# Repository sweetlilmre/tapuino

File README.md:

# Tapuino

This project is now in maintanence mode and has been superseeded by the [Tapuino Next](https://github.com/sweetlilmre/TapuinoNext)

However amazing people keep building this version and adding value (see the [3D printable enclosure below](#3d-printable-enclosure))

Limited support can be found in the following Amibay forum [Amibay](https://www.amibay.com/threads/tapuino-the-20-c64-tape-emulator.64874)

## The $20 C64 Tape Emulator

Details can be found on my blog: http://www.sweetlilmre.com

The FAQ and other docs can be found on the wiki: https://github.com/sweetlilmre/tapuino/wiki

A really nice board design can be found here: https://github.com/arananet/tapuinomini1.03

And a write up here: http://arananet-net.kinja.com/tapuino-1-03-mejorando-el-tapuino-mini-1788202676

These schematics are also provided in the "layout" folder as a convenience. 

Portions of this code are copyright by their respective owners:

 * PetitFatfs: Chan: http://elm-chan.org/fsw/ff/00index_p.html
 * I2C code: Peter Fleury <pfleury@gmx.ch>  http://jump.to/fleury
 * LCD code: conversion of the Arduino code apparently by DFRobot? (converted to C by me)

## 3D printable enclosure
by @fabriziofiorucci

A [3D printable enclosure](CAD) designed with Fusion 360 is available for download as .stl files

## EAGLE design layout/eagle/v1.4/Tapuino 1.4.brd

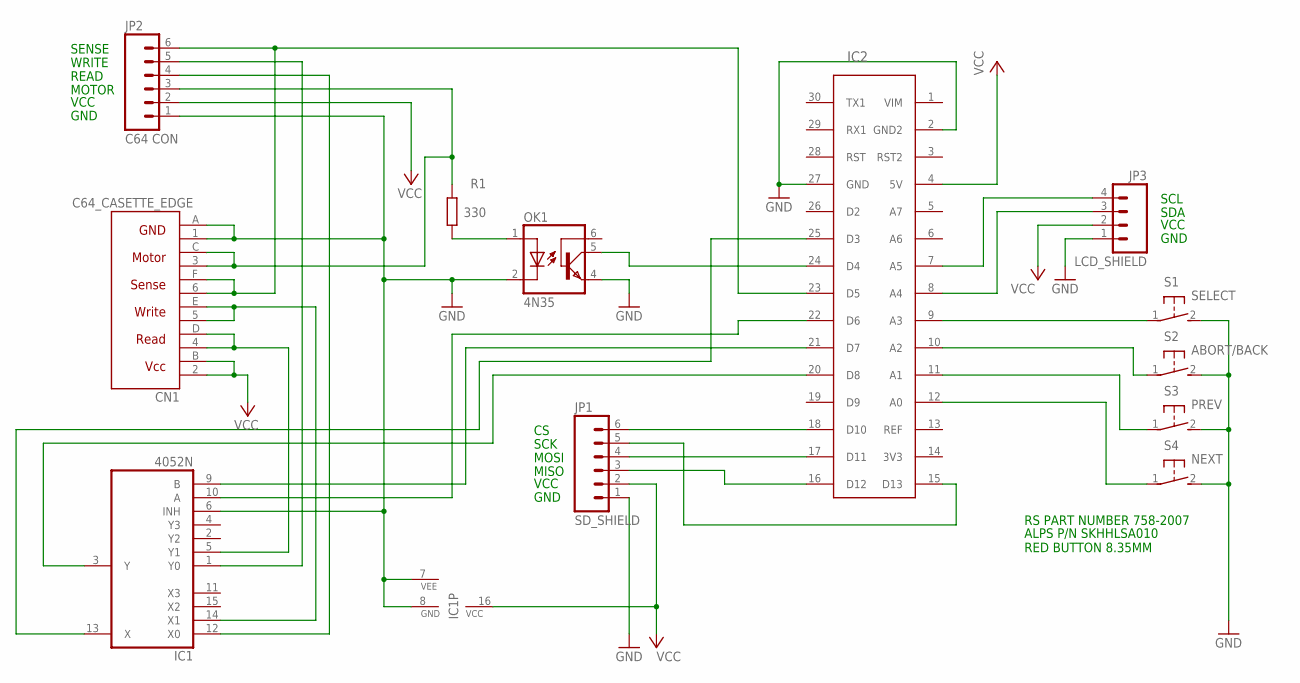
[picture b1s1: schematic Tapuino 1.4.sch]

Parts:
CN1: C64_CASETTE_EDGE; C64_CASSETTE
IC1: 4052N; DIL16
IC2: ARDUINO_NANO_V3; NANO_V3
JP1: SD_SHIELD; 1X06_LOCK_LONGPADS
JP2: C64 CON; 1X06_LOCK_LONGPADS
JP3: LCD_SHIELD; 1X04_LOCK_LONGPADS
OK1: 4N35; DIL06
R1: 330; 0207/10
S1: SELECT; B3F-31XX
S2: ABORT/BACK; B3F-31XX
S3: PREV; B3F-31XX
S4: NEXT; B3F-31XX

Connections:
GND: CN1.1 (GND1), CN1.A (GND2), IC1.6 (INH), IC1.7 (VEE), IC1.8 (GND), IC2.2 (GND2), IC2.27 (GND), JP1.1, JP2.1, JP3.1, OK1.2 (C), OK1.4 (EMI), S1.2 (S), S2.2 (S), S3.2 (S), S4.2 (S)
unnamed: IC2.16 (D12), JP1.3
unnamed: IC2.18 (D10), JP1.6
unnamed: IC2.15 (D13), JP1.5
unnamed: IC2.17 (D11), JP1.4
unnamed: IC2.7 (A5), JP3.4
unnamed: IC2.8 (A4), JP3.3
unnamed: IC2.9 (A3), S1.1
unnamed: OK1.1 (A), R1.1
unnamed: IC2.12 (A0), S4.1
unnamed: IC2.24 (D4), OK1.5 (COL)
unnamed: IC2.11 (A1), S3.1
unnamed: IC1.1 (Y0), JP2.5
unnamed: CN1.3 (MOTOR1), CN1.C (MOTOR2), JP2.3, R1.2
unnamed: IC1.3 (Y), IC2.20 (D8)
unnamed: IC1.12 (X0), JP2.4
unnamed: CN1.6 (SENSE1), CN1.F (SENSE2), IC2.23 (D5), JP2.6
unnamed: IC1.13 (X), IC2.25 (D3)
unnamed: CN1.4 (READ1), CN1.D (READ2), IC1.5 (Y1)
unnamed: IC1.9 (B), IC2.21 (D7)
unnamed: CN1.5 (WRITE1), CN1.E (WRITE2), IC1.14 (X1)
unnamed: IC1.10 (A), IC2.22 (D6)
unnamed: IC2.10 (A2), S2.1
VCC: CN1.2 (VCC1), CN1.B (VCC2), IC1.16 (VCC), IC2.4 (5V), JP1.2, JP2.2, JP3.2

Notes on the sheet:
SCK
MOSI
MISO
VCC
GND
SCL
SDA
SENSE
WRITE
READ
MOTOR
RS PART NUMBER 758-2007
ALPS P/N SKHHLSA010 RED BUTTON 8.35MM

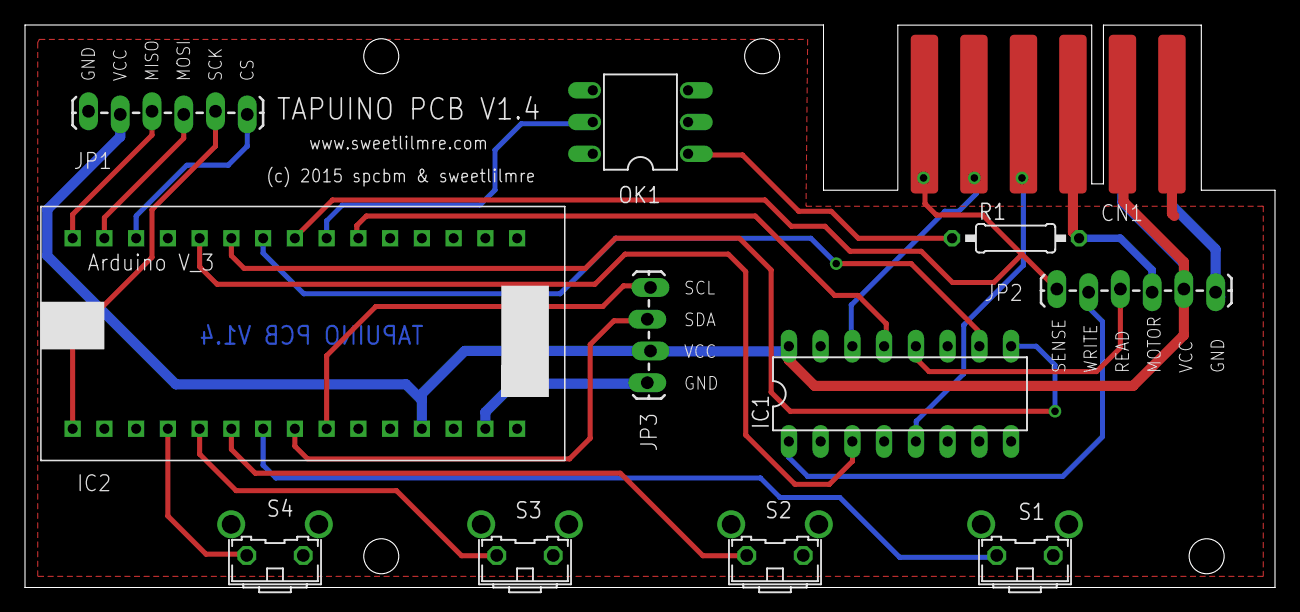
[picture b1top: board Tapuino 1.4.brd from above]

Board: 2 copper layers, 100.0 x 45.0 mm, 12 parts (0 on the bottom side), 24 nets.

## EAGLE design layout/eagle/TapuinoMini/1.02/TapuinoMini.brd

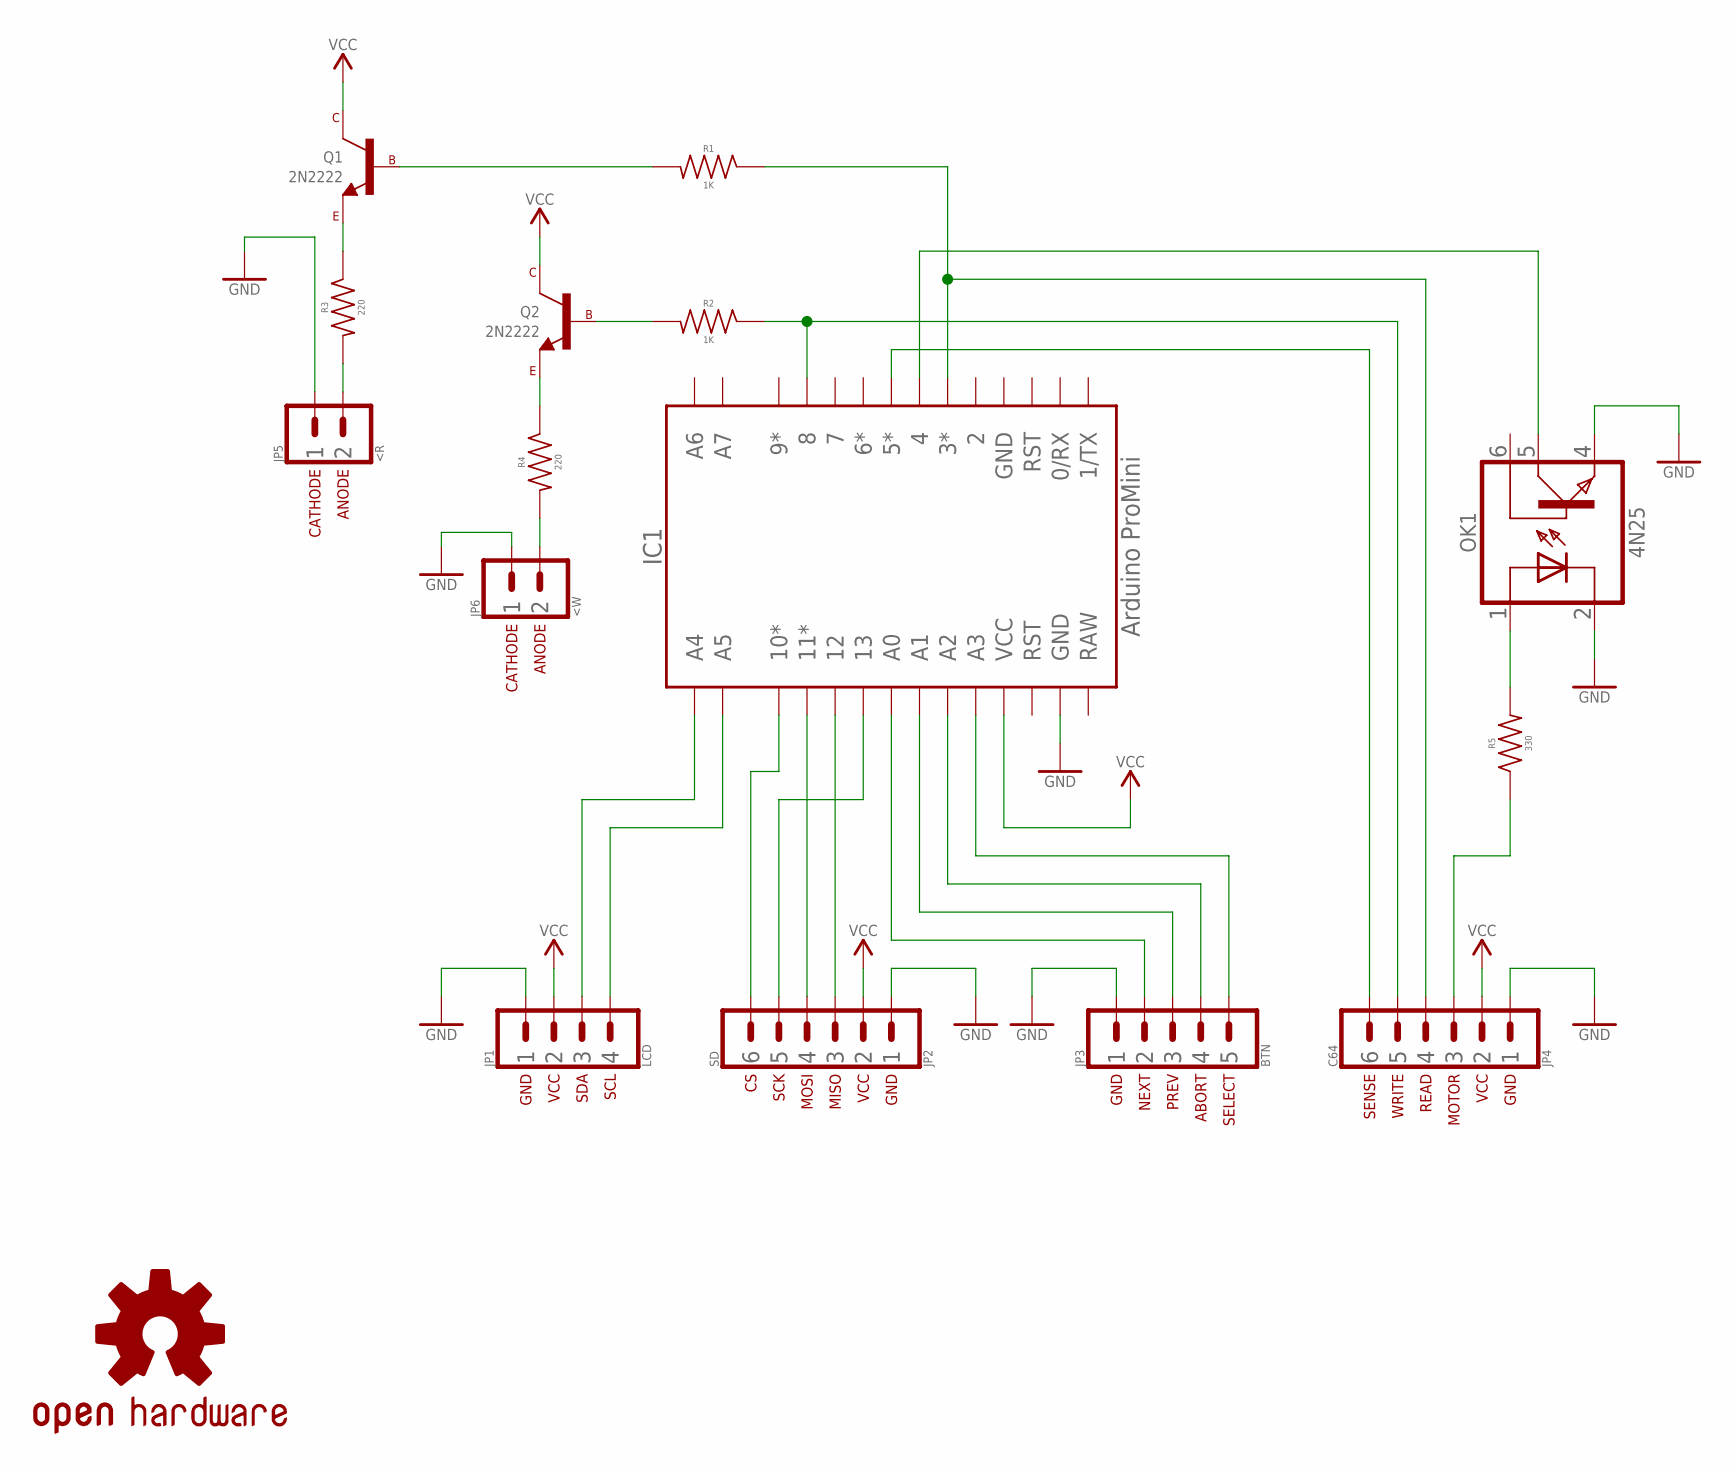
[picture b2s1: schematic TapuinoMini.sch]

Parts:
IC1: Arduino ProMini; PROMINI_A
JP1: LCD; 1X04_SQR
JP2: SD; 1X06_SQR
JP3: BTN; 1X05_SQR
JP4: C64; 1X06_SQR
JP5: <R; 1X02_SQR
JP6: <W; 1X02_SQR
LOGO1: OSHW-LOGOL; OSHW-LOGO-L
OK1: 4N25; DIP06
Q1, Q2: 2N2222; TO-92
R1, R2: 1K; RESISTOR_PTH_0.3
R3, R4: 220; RESISTOR_PTH_0.3
R5: 330; RESISTOR_PTH_0.3

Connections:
ABORT: IC1.A2, JP3.4
CS: IC1.10*, JP2.6
GND: IC1.GND@1 (GND), JP1.1, JP2.1, JP3.1, JP4.1, JP5.1, JP6.1, OK1.2 (CATHODE), OK1.4 (EMITTER)
MISO: IC1.12, JP2.3
MOSI: IC1.11*, JP2.4
MOTOR1: JP4.3, R5.1
MOTOR2: OK1.1 (ANODE), R5.2
MOTOR3: IC1.4, OK1.5 (COLLECTOR)
NEXT: IC1.A0, JP3.2
PREV: IC1.A1, JP3.3
READ1: IC1.3*, JP4.4, R1.1
READ2: Q1.2 (BASE), R1.2
READ3: Q1.1 (EMITTER), R3.1
READ4: JP5.2, R3.2
SCK: IC1.13, JP2.5
SCL: IC1.A5, JP1.4
SDA: IC1.A4, JP1.3
SELECT: IC1.A3, JP3.5
SENSE: IC1.5*, JP4.6
VCC: IC1.VCC, JP1.2, JP2.2, JP4.2, Q1.3 (COLLECTOR), Q2.3 (COLLECTOR)
WRITE1: IC1.8, JP4.5, R2.1
WRITE2: Q2.2 (BASE), R2.2
WRITE3: Q2.1 (EMITTER), R4.1
WRITE4: JP6.2, R4.2

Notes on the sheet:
GND
VCC
SDA
SCL
SCK
MISO
MOSI
NEXT
PREV
ABORT
SELECT
MOTOR
READ
WRITE
SENSE
CATHODE
ANODE

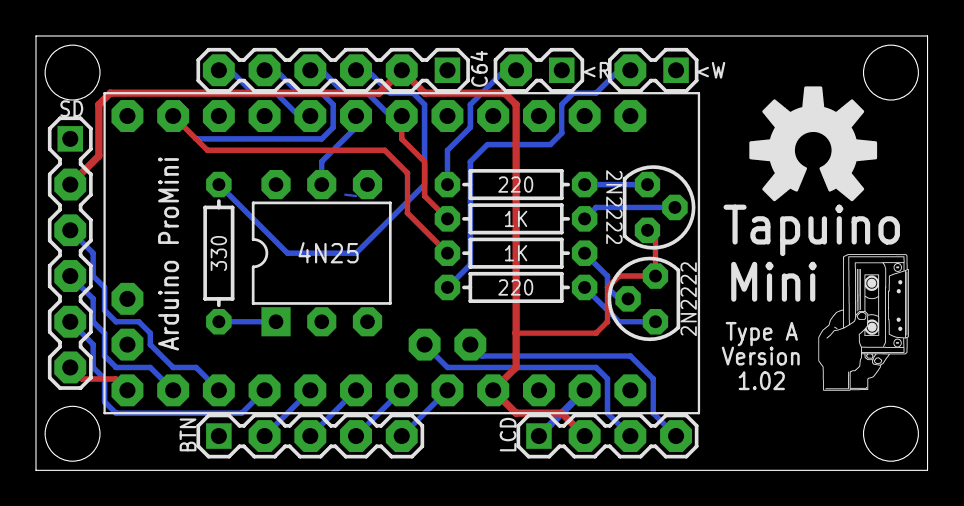
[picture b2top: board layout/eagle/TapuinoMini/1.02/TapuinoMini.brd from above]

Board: 2 copper layers, 49.5 x 24.1 mm, 16 parts (0 on the bottom side), 24 nets.

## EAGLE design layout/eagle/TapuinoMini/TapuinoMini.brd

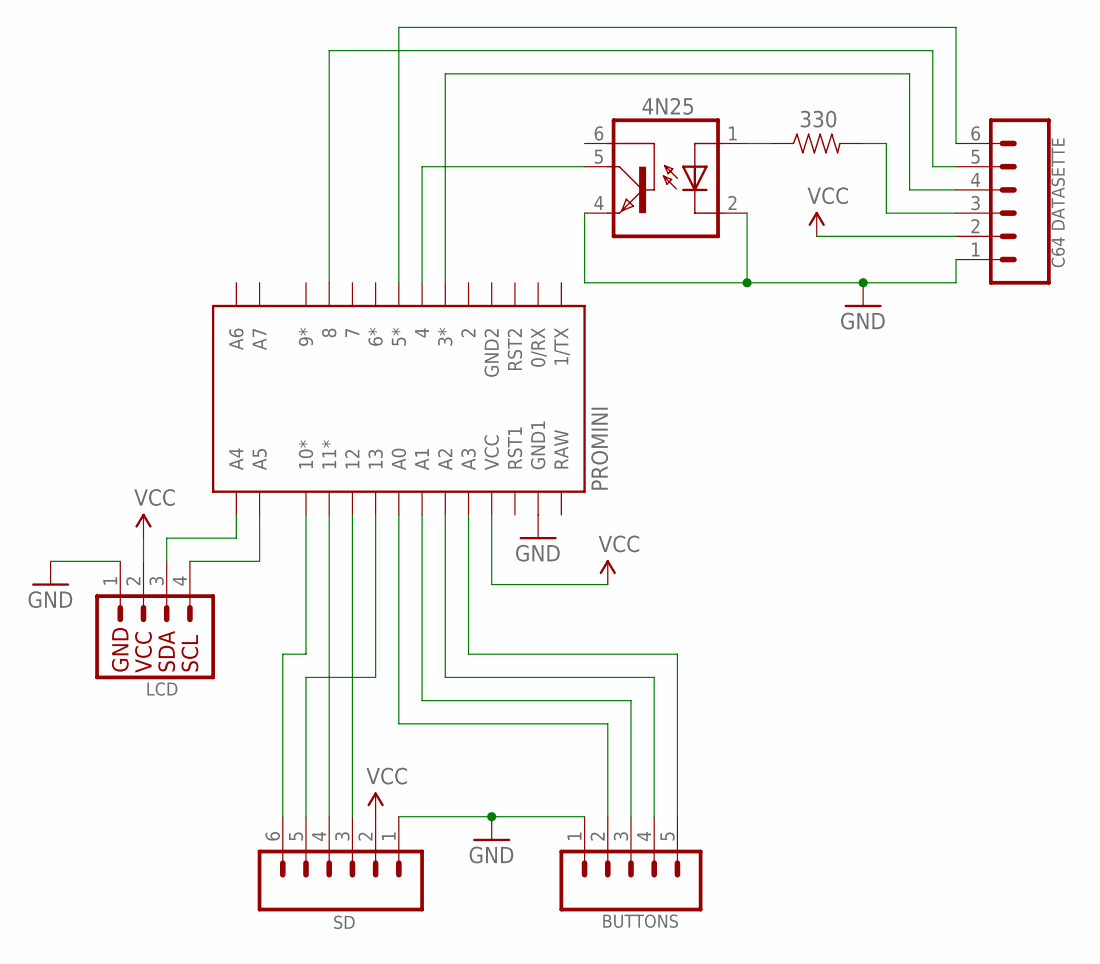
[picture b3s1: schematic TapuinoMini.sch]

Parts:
JP1: C64 DATASETTE; 1X06
JP2: SD; 1X06
JP3: BUTTONS; 1X05
JP4: LCD; 1X04
OK1: 4N25; DIL06
PROMINI: PROMINI_A
R1: 330; AXIAL-0.3

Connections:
GND: JP1.1, JP2.1, JP3.1, JP4.1, OK1.2 (C), OK1.4 (EMI), PROMINI.GND1
unnamed: JP3.5, PROMINI.A3
unnamed: JP3.4, PROMINI.A2
unnamed: JP3.3, PROMINI.A1
unnamed: JP3.2, PROMINI.A0
unnamed: JP2.3, PROMINI.12
unnamed: JP2.4, PROMINI.11*
unnamed: JP2.6, PROMINI.10*
unnamed: JP2.5, PROMINI.13
unnamed: JP4.4, PROMINI.A5
unnamed: JP4.3, PROMINI.A4
unnamed: JP1.3, R1.P$2 (2)
unnamed: OK1.1 (A), R1.P$1 (1)
unnamed: JP1.4, PROMINI.3*
unnamed: OK1.5 (COL), PROMINI.4
unnamed: JP1.5, PROMINI.8
unnamed: JP1.6, PROMINI.5*
VCC: JP1.2, JP2.2, JP4.2, PROMINI.VCC

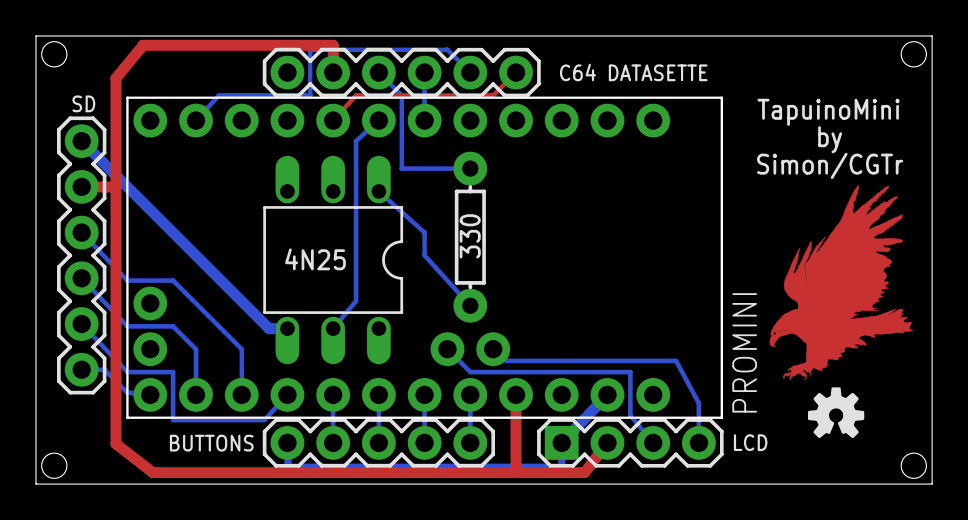
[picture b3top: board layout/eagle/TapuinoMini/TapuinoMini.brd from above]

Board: 2 copper layers, 49.8 x 24.9 mm, 9 parts (0 on the bottom side), 18 nets.

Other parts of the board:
U$2: EAGLE-TOP-8MM
U$3: OSHW-LOGO-S

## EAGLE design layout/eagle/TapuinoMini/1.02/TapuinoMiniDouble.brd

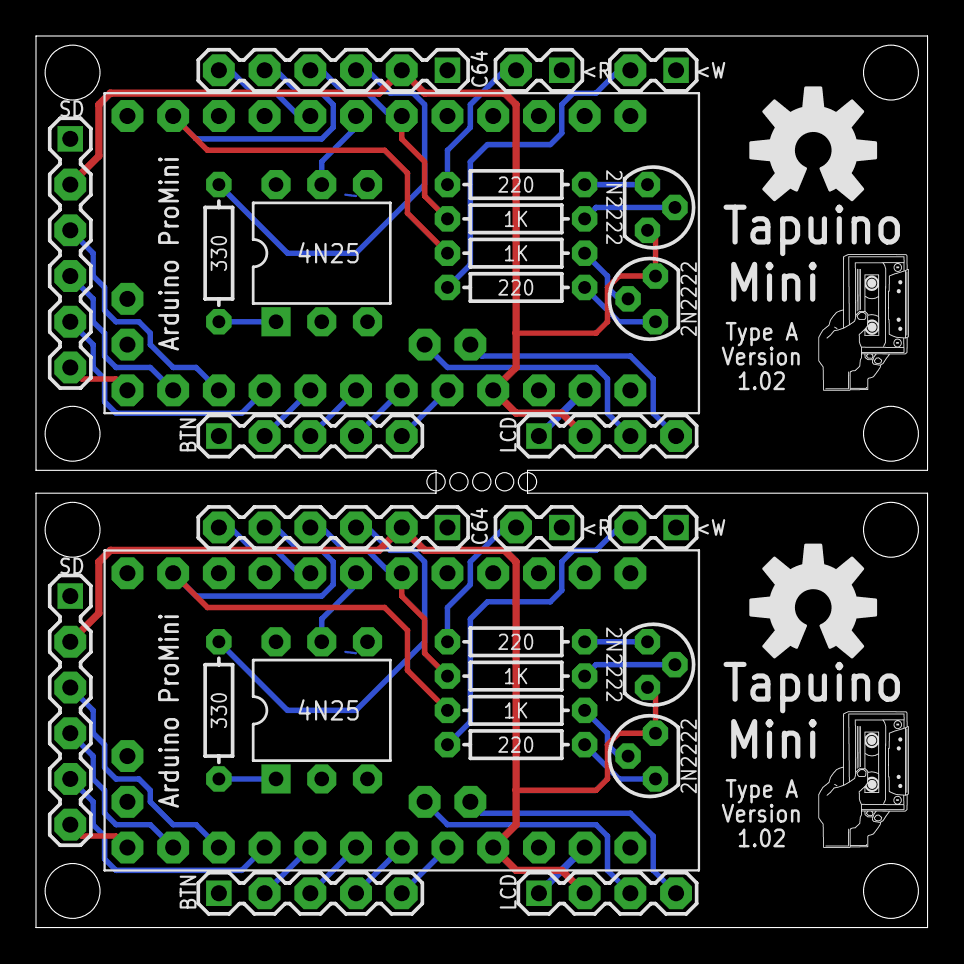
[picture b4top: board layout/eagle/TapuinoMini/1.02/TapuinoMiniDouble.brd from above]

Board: 2 copper layers, 49.5 x 49.5 mm, 32 parts (0 on the bottom side), 48 nets.

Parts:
IC1, IC2: Arduino ProMini; PROMINI_A
JP1, JP7: LCD; 1X04_SQR
JP2, JP8: SD; 1X06_SQR
JP3, JP9: BTN; 1X05_SQR
JP4, JP10: C64; 1X06_SQR
JP5, JP11: <R; 1X02_SQR
JP6, JP12: <W; 1X02_SQR
LOGO1, LOGO2: OSHW-LOGOL; OSHW-LOGO-L
OK1, OK2: 4N25; DIP06
Q1, Q2, Q3, Q4: 2N2222; TO-92
R1, R2, R7, R8: 1K; RESISTOR_PTH_0.3
R3, R4, R9, R10: 220; RESISTOR_PTH_0.3
R5, R6: 330; RESISTOR_PTH_0.3

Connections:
ABORT: IC1.A2, JP3.4
ABORT1: IC2.A2, JP9.4
CS: IC1.10*, JP2.6
CS1: IC2.10*, JP8.6
GND: IC1.GND@1, JP1.1, JP2.1, JP3.1, JP4.1, JP5.1, JP6.1, OK1.2, OK1.4
GND1: IC2.GND@1, JP7.1, JP8.1, JP9.1, JP10.1, JP11.1, JP12.1, OK2.2, OK2.4
MISO: IC1.12, JP2.3
MISO1: IC2.12, JP8.3
MOSI: IC1.11*, JP2.4
MOSI1: IC2.11*, JP8.4
MOTOR1: JP4.3, R5.1
MOTOR2: OK1.1, R5.2
MOTOR3: IC1.4, OK1.5
MOTOR4: JP10.3, R6.1
MOTOR5: OK2.1, R6.2
MOTOR6: IC2.4, OK2.5
NEXT: IC1.A0, JP3.2
NEXT1: IC2.A0, JP9.2
PREV: IC1.A1, JP3.3
PREV1: IC2.A1, JP9.3
READ1: IC1.3*, JP4.4, R1.1
READ2: Q1.2, R1.2
READ3: Q1.1, R3.1
READ4: JP5.2, R3.2
READ5: IC2.3*, JP10.4, R7.1
READ6: Q3.2, R7.2
READ7: Q3.1, R9.1
READ8: JP11.2, R9.2
SCK: IC1.13, JP2.5
SCK1: IC2.13, JP8.5
SCL: IC1.A5, JP1.4
SCL1: IC2.A5, JP7.4
SDA: IC1.A4, JP1.3
SDA1: IC2.A4, JP7.3
SELECT: IC1.A3, JP3.5
SELECT1: IC2.A3, JP9.5
SENSE: IC1.5*, JP4.6
SENSE1: IC2.5*, JP10.6
VCC: IC1.VCC, JP1.2, JP2.2, JP4.2, Q1.3, Q2.3
VCC1: IC2.VCC, JP7.2, JP8.2, JP10.2, Q3.3, Q4.3
WRITE1: IC1.8, JP4.5, R2.1
WRITE2: Q2.2, R2.2
WRITE3: Q2.1, R4.1
WRITE4: JP6.2, R4.2
WRITE5: IC2.8, JP10.5, R8.1
WRITE6: Q4.2, R8.2
WRITE7: Q4.1, R10.1
WRITE8: JP12.2, R10.2

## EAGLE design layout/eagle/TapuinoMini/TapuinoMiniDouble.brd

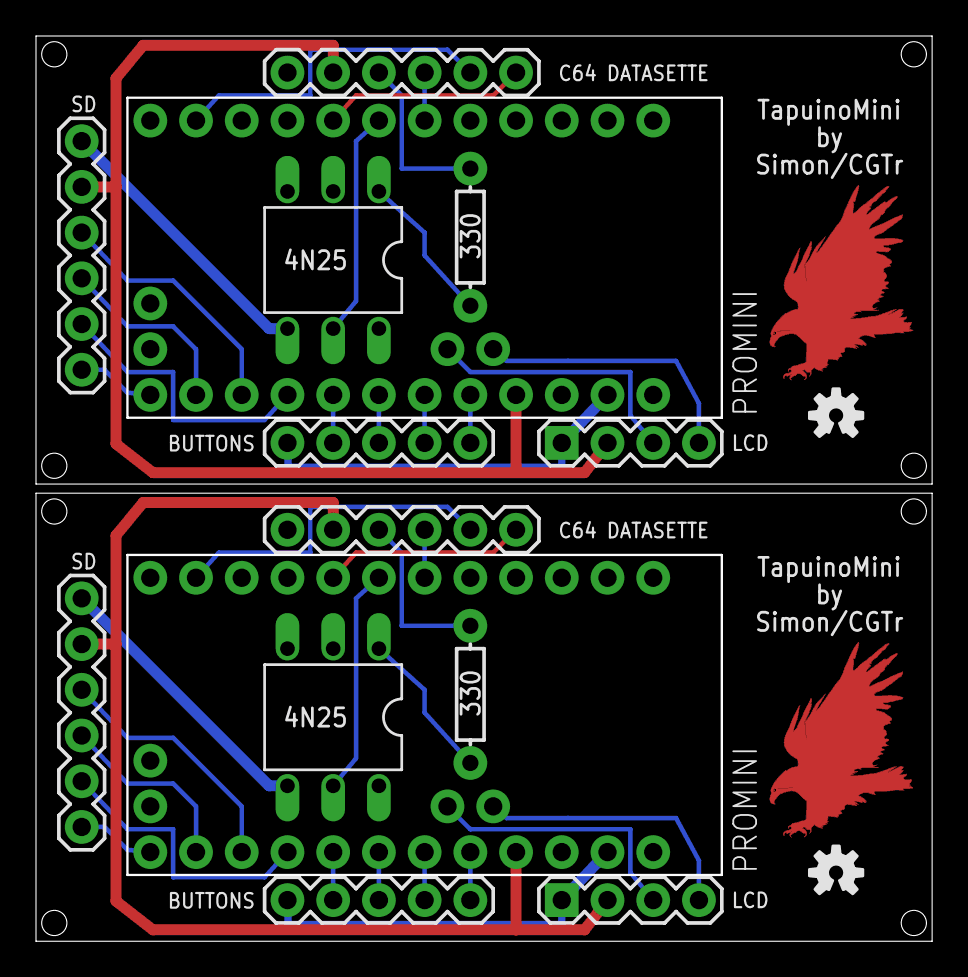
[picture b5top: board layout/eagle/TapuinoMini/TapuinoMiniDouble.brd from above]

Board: 2 copper layers, 49.8 x 50.3 mm, 18 parts (0 on the bottom side), 36 nets.

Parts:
JP1, JP8: C64 DATASETTE; 1X06
JP2, JP5: SD; 1X06
JP3, JP6: BUTTONS; 1X05
JP4, JP7: LCD; 1X04
OK1, OK2: 4N25; DIL06
PROMINI, PROMINI1: PROMINI_A
R1, R2: 330; AXIAL-0.3
U$1, U$2: EAGLE-TOP-8MM
U$3, U$4: OSHW-LOGO-S

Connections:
GND: JP1.1, JP2.1, JP3.1, JP4.1, OK1.2, OK1.4, PROMINI.GND1
GND1: JP5.1, JP6.1, JP7.1, JP8.1, OK2.2, OK2.4, PROMINI1.GND1
unnamed: JP3.5, PROMINI.A3
unnamed: JP3.4, PROMINI.A2
unnamed: JP3.3, PROMINI.A1
unnamed: JP3.2, PROMINI.A0
unnamed: JP2.3, PROMINI.12
unnamed: JP2.4, PROMINI.11*
unnamed: JP2.6, PROMINI.10*
unnamed: JP2.5, PROMINI.13
unnamed: JP4.4, PROMINI.A5
unnamed: JP4.3, PROMINI.A4
unnamed: JP1.3, R1.P$2
unnamed: OK1.1, R1.P$1
unnamed: JP1.4, PROMINI.3*
unnamed: OK1.5, PROMINI.4
unnamed: JP1.5, PROMINI.8
unnamed: JP1.6, PROMINI.5*
unnamed: JP6.5, PROMINI1.A3
unnamed: JP6.4, PROMINI1.A2
unnamed: JP6.3, PROMINI1.A1
unnamed: JP6.2, PROMINI1.A0
unnamed: JP5.3, PROMINI1.12
unnamed: JP5.4, PROMINI1.11*
unnamed: JP5.6, PROMINI1.10*
unnamed: JP5.5, PROMINI1.13
unnamed: JP7.4, PROMINI1.A5
unnamed: JP7.3, PROMINI1.A4
unnamed: JP8.3, R2.P$2
unnamed: OK2.1, R2.P$1
unnamed: OK2.5, PROMINI1.4
unnamed: JP8.4, PROMINI1.3*
unnamed: JP8.5, PROMINI1.8
unnamed: JP8.6, PROMINI1.5*
VCC: JP1.2, JP2.2, JP4.2, PROMINI.VCC
VCC1: JP5.2, JP7.2, JP8.2, PROMINI1.VCC

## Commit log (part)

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2014-06-27 SPI Full speed fix and Timer rewrite (3rd time :()
2014-06-29 Working on directory traversal
2014-06-29 moving to indexed file selection and commit for crash recovery on my machine!
2014-06-29 prev / next file seek working
2014-06-29 added '..' navigation for directory traversal
2014-06-29 Added directory display handling and cleanup after send
2014-06-30 Move lcd handling to utils, part of a slow bigger cleanup Added proper motor handling Made memstrings sharable
2014-07-02 Changed motor signal handling for new opto-coupler handling
2014-07-03 added missing config.h
2014-07-03 Removed length check timing, its still not working :(
2014-07-03 added missing tapuino.h
2014-07-03 added missing memstrings.c
2014-07-04 added button support and moved some config to config.h 2 line lcd now supported through config.h
2014-07-13 renames and cleanup. fixed exit condition for motor off timeout reduced display string length for 16x2 displays increased debounce time
2014-07-15 Added design files to layout folder Added write pin definition
2014-07-15 added button layouts
2014-07-17 refactored file functions into fileutils.c added in proper end of TAP check added timing defines for possible NTSC compliance added loading percent indicator
2014-07-17 added missing license
2014-07-17 fixed LICENCE and README.md
2014-07-17 changed all line endings to UNIX format for sanity
2014-07-17 fixed some strings
2014-07-17 oops! added missing break statement.
2014-07-22 Moved SD Card handling to fatfs Introduced filename ticker Cleaned up LCD code
2014-07-22 more cleanup
2014-07-23 added serial debugging to determine if I2C init is failing
2014-07-23 added I2C debugging statements over serial
2014-07-24 added I2C pullup init to fix I2C init issue on Funduino LCM1602 board
2014-07-24 removed lcd debugging output over serial
2014-07-24 re-arranging, starting multi-menu support
2014-07-24 TAP write code, first attempt.
2014-07-27 Fixed SD timeout handling for write Moved menu ui and handling into separate code files Added initial write code, doesn't work yet
2014-07-27 added missing menu files
2014-07-27 fixed write offset issues for TAP writing (length is now correct) fixed port config for write pin
2014-07-27 First successful write code!!!! various fixes serial baud rate changed to 57600
2014-07-28 updated Fritizing file and image
2014-08-03 Added fix for long loader and possibly multiload games
2014-08-04 Moved all dodgy timing to use system 10ms timer Added key repeat functionality Cleaned up comms, serial is removed now
2014-08-07 first pass on lcd config and manual filename entry
2014-08-07 LCD configuration now in config.h for I2C expander bit mapping
2014-08-07 A good stab at handling manual file names, much more to be done
2014-08-11 Added short and long key press detection code Bug fix: added missing sense signal OFF after record
2014-08-11 moved busy_spinner to lcdutils.c for use by comms.c test for ABORT long in record menu
2014-08-11 code optimizations first complete attempt at manual naming
2014-08-11 well the last commit wasn't very clever, lets try again
2014-08-11 that worked! cleanup of filename handling in record function
2014-08-11 fix for blank entries after a recording removed pointless memstring optimization removed unnecessary memstrings
2014-08-11 Mode mode transitions fixups
2014-08-20 Fixed menu flow for recording Fixed missing zero terminator in lcdutils when writing the status line Reworded some strings Added initial support for signal inversion (only playback and hardcoded atm)
2014-08-21 Changed all config.h timing value to millisecond Fixed filename_ticker for millisecond values and line length Made strings less verbose to save flash space Added basic option value code
2014-08-21 Option code in for 1 option Started removing serial code for more flash space
2014-08-22 FIX: forgot to mark g_invert_signal extern...
2014-08-22 All options implemented EEPROM saving implemented Record mode signal inversion added
2014-08-23 FIX: Ticker bug where filename wouldn't start at first character
2014-08-23 modified eeprom save function to use eeprom_update_byte (let's save the eeprom!) removed Unicode table handling from FatFs, over 1K more free
2014-08-25 Changed recording mode to use 1/6th uS resolution, makes muuuch better TAPs
2014-10-04 Added control line setup Minor memory optimizations
2014-10-12 Control line code for MUX switching Fixed PROGMEM references for Atmel Studio Added Atmel Studio project files Added new and updated schematic and fritzing files
2014-12-08 fixed casing for lcd.h include in lcd.c
2014-12-12 Added Tapuino Eagle files
2015-01-03 Minor changes to mux board
2015-01-07 added fixed nano v3 and commodore parts for eagle
2015-01-20 Tapuino 1.2. board layout added
2015-01-20 Added spcbm 1.2 board, removed mine
2015-01-20 minor cleanup for spcbm 1.2
2015-01-24 removed url until I know what the official one is
2015-01-24 added layout LICENCE
2015-02-14 Update config.h
    create config parameter for internal pullup resistors (HW 2.0)
2015-02-14 Update comms.c
    added HW 2.0 configurable support
2015-02-14 Update menu.c
    updated player mode. directory now will not change when aborting tap file.
2015-02-14 Update config.h
    added config option for HW 2.0
2015-02-14 Update config.h
    added config option for HW 2.0 boards
2015-02-14 Update comms.c
    added key support for HW 2.0 board
2015-02-14 Fixed 'command leakage' when playback was aborted which caused the menu to go up a dir. Some minor cleanup of tabs and indentation
2015-02-25 Special handling for TAP format 0. Fixed command leakage from recording mode
2015-03-07 Made V2 hardware (internal pullups) the default behaviour Made serial compilation conditional via config.h
2015-03-07 Cleaning up layout folders
2015-03-07 More cleanup on layout
2015-03-07 added missing 1.4 board files
2015-03-16 added missing and updated r2 images
2015-03-22 Rework of the LCD drivers to allow for support for various other I2C based displays Fix for button board layout
2015-03-27 Fixed bug where recording would not work on a blank formatted SD Card i.e. there had to be at least one file / folder on the card Made creation of recorded folder part of startup.
2015-03-27 reverted to standard LCD module
2015-03-28 Cleaning up some dead code
2015-04-02 Added Mini design files by ozayturay
2015-04-05 Added: initial OLED driver refactored code to use tap header and be aware of C16 TAP files (support is not complete yet)
2015-04-05 Fix: various warnings and line ending consistency
2015-04-16 added Italian memstrings file
2015-04-16 renamed memstrings Italian to avoid compile conflict
2015-04-16 Update memstrings.c-it
    better translation, revert "salvataggio" to "record" for compatibility, italians c64 fan does know what "record" mean :D
2015-04-17 first bit of counter code
2015-04-18 Testing out half-wave code
2015-04-18 doubled signal length for half-wave TAP format at 2Mhz timer
2015-04-18 Expanded cycle timing macros for readability
2015-04-20 Bugfix for Format 2 support (half-waves) Work around for TAPs with bizarre length values in the header Clean-up of cycle handling for different machines
2015-04-20 credit added for clever define check
2015-04-21 Update memstrings.c-it
    updated Italian translation for "Invalid Size" Thanks @juri74
2015-04-28 added changes for selectable machine type via settings, this implemented different cycle timing for C16 compatibility
2015-04-28 Updated TapuinoMini Eagle design files in layout folder.
2015-05-04 Update memstrings.c-it
2015-05-04 Update tapuino.c
    fixed save header for c16 tap format compatibility ($02 @ $0D)
2015-05-05 changed incorrect comment on machine type in TAP_INFO struct
2015-05-07 Added version information and code Moved Neutral strings into separate file
2015-05-15 LCD interface cleanup - preparation for different LCD models
2015-05-16 rename for consistency
2015-05-16 bump version
2015-05-17 Added 1306 display module and font.
2015-05-17 fixed line endings in version.h
2015-05-24 Moved user config to config-user.h with config-user.h.example as a template moved language files and added preprocessor guards to allow for configurable language Fixed some compiler warnings for miss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
2015-05-25 Added Pause function. SELECT button will toggle pause mode, 'P' will be displayed on the LCD
2015-06-05 added recording LED config and code
2015-06-05 bumped version
2015-08-16 Added Auto Finalize option fixed option handling in menu.c to remember last select option when exiting from a specific option menu
2015-08-17 Fixed translation Fixed complete message
2015-08-19 Fixed bug when ABORT was pressed in Select Mode menu Potential fix to prevent LONG pauses when recording using manual finalize mode with multiple blocks and motor stops (rainbow islands masterings so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
2015-08-20 Added Turkish memstrings file and associated config options
2015-08-20 Update version.h
    bumped version to reflect Turkish translation
2016-01-04 removed tabs, properly cased integer.h include for real OS' :)
2016-01-10 rotary encoder support, define USE_ROTARY_ENCODER to use
2016-01-10 fixed config-user.h.example for USE_ROTARY_ENCODER define removed illogical test in comms.c
2016-01-10 direct encoder polling for accuracy
2016-06-13 Añado soporte idioma español
2016-06-13 Añado soporte idioma español y fichero memstring en español
2016-09-23 Add german translation
2016-09-23 Add makefile utilizing arduino-builder and avrdude
2016-10-04 tapuino.h
    Changed a few external declarations to fix compiler warnings. Actually, 4 externals where changed from uint8 to uint16.
2016-10-31 Update README.md
    added mini design
2016-11-02 Added Tapuino Mini schematics
2016-11-02 updated readme to reflect the location of the Tapuino Mini schematics
2017-12-09 minor fix to 1602 OLED module to add a small delay post I2C init for init stability version bump
2017-12-11 Fixed SSD131x driver compile fail (rename of i2cmster.h to i2c_master.h)
2017-12-25 adding gitattibutes file in an attempt to have the repo correctly classified
2017-12-26 changed READ and WRITE lines to LOW to avoid lighting LEDs on aranet board
2018-01-25 added switchable font size for SSD1306 oled, defined by LCD_SSD1306_BIG_FONTS in config-user.h
2018-01-25 forgot to bump version
2018-05-05 Cleaned up the SSD1306 code and added support for 128x32 sized displays Added defines to config.h and config-user.h.example to support this
2018-05-06 Updated version,h for SSD1306 changes
2019-09-16 Format "thanks" section
    The line breaks looked a little odd on the web GitHub client
2019-11-20 Save much needed SRAM by moving FatFs LUT to PGM space.
2019-11-20 Don't rely on uninitialized varible (br) being non-zero.
2019-11-22 Refactor (mostly unused) g_tap_info
2019-11-22 Remove unused variable g_key_repeat_start
2019-11-22 Refactor TAP send ISR
2020-05-28 add a fontconverter to generate the font8x16.h file that is used for big fonts on small (128x32) SSD1306 displays
2020-05-28 use the 8x16 font for small (128x32) SSD1306 displays if LCD_SSD1306_BIG_FONTS is defined.
2022-01-27 Fixed uninitialized variable check (br) in play_file() and initial buffer read in verify_tap() Moved FatsFS buffer into flash storage Commented unused config setting g_key_repeat_start Changes sugges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
2022-02-01 Update version.h
    updated version for new release
2022-02-01 TAP play ISR refactor
2022-02-02 comment updates
2022-02-10 Refactor playback ISR thanks to @matsstaff (#45)
    * TAP play ISR refactor
    * comment updates
2022-02-11 minor comment updates
2023-02-13 Added enclosuer STL files for 3d printing
2023-02-17 Files structure updated
2023-02-17 README updated
2023-02-17 Update README.md
    Made the readme neater and kept the maintenance mode notice
2023-02-17 Added 3d printable enclosure (#49)
    * Added enclosuer STL files for 3d printing
    * Added enclosuer STL files for 3d printing
    * Files structure updated
    * README updated
    * README updated
    * README updated
2024-07-21 Handle Sense pin in an open-collector fashion
2024-07-21 Fix description

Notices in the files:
layout/eagle/v1.4/Tapuino 1.4.brd:
(c) 2015 spcbm & sweetlilmre
parts and their libraries:
SparkFun-Connectors: Licensing: Creative Commons ShareAlike 4.0 International - https://creativecommons.org/licenses/by-sa/4.0
SparkFun: Licensing: CC v3.0 Share-Alike You are welcome to use this library for commercial purposes.
